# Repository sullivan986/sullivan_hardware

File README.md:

# sullivan_hardware
Some open-source hardware designed by Kicad.

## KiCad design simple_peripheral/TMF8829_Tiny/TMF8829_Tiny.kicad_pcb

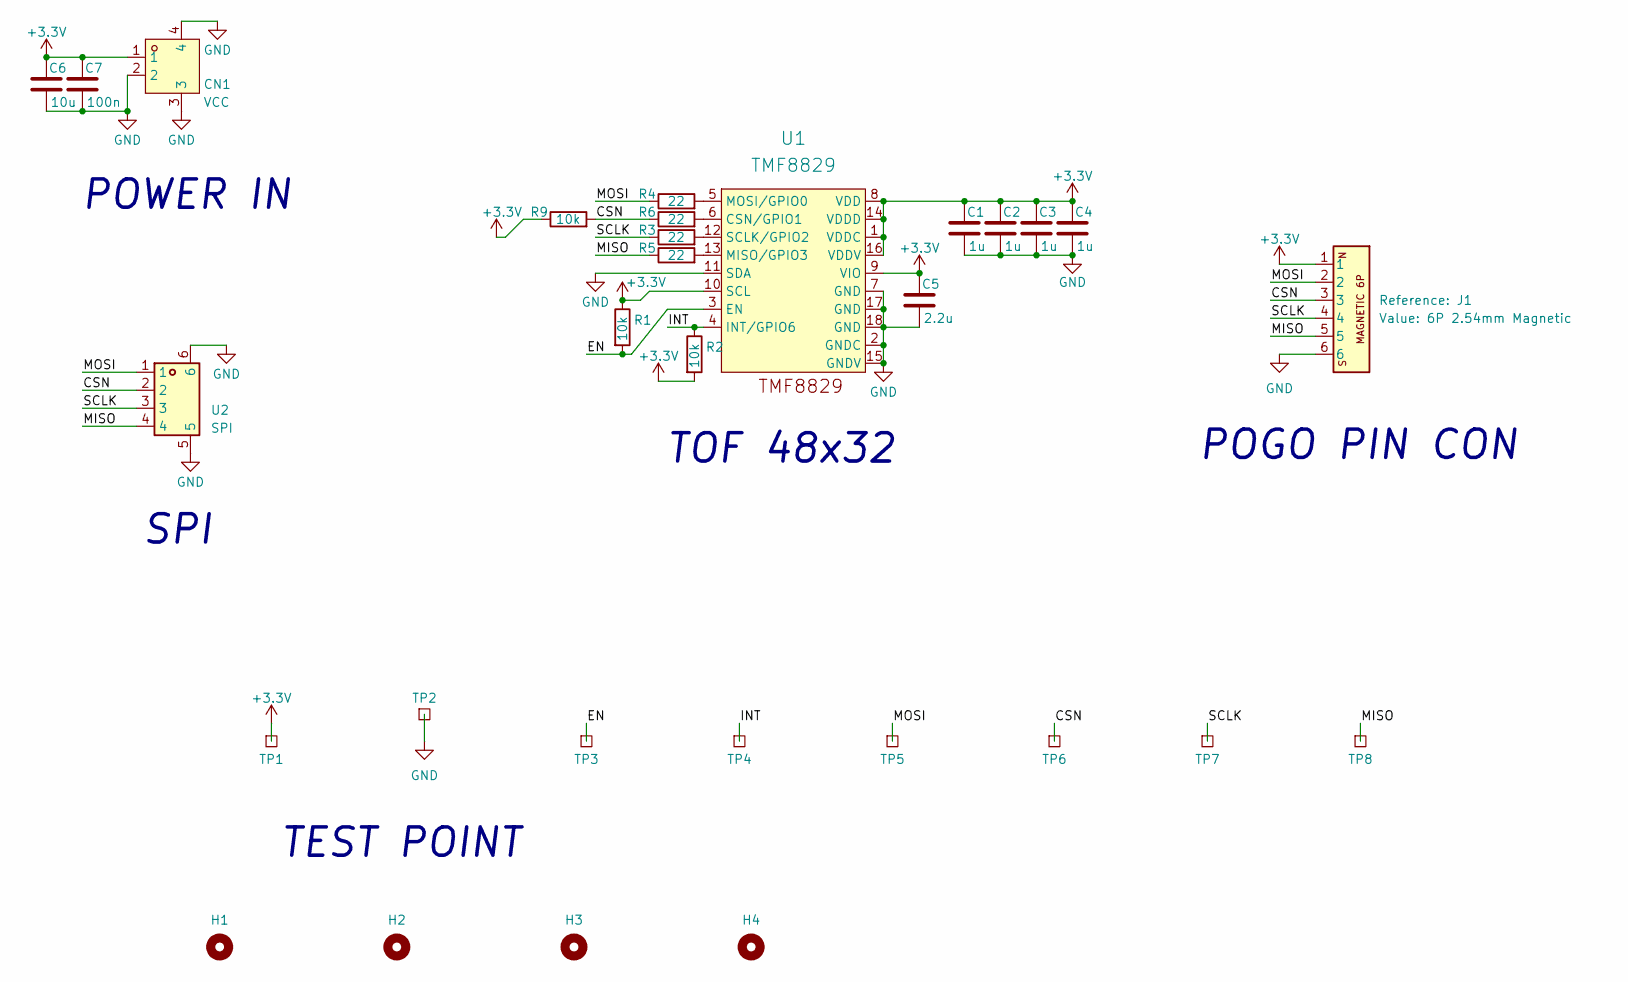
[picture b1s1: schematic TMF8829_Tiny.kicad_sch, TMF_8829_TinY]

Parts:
C1, C2, C3, C4: 1u; C_0402_1005Metric
C5: 2.2u; C_0402_1005Metric
C6: 10u; C_0402_1005Metric
C7: 100n; C_0402_1005Metric
CN1: VCC; CONN-TH_2P-P1.25_XUNPU_WAFER-GH1.25-2PWB; MPN WAFER-GH1.25-2PWB; LCSC Part C3029377
H1, H2, H3, H4: MountingHole; MountingHole_2.2mm_M2
J1: 6P 2.54mm Magnetic; Connector_Magnetic_1x06_P2.54mm_RA
R1, R2, R9: 10k; R_0402_1005Metric
R3, R4, R5, R6: 22; R_0402_1005Metric
TP1: 3V3; TestPoint_Pad_2.0x2.0mm
TP2: GND; TestPoint_Pad_2.0x2.0mm
TP3: EN; TestPoint_Pad_2.0x2.0mm
TP4: INT; TestPoint_Pad_2.0x2.0mm
TP5: MOSI; TestPoint_Pad_2.0x2.0mm
TP6: CSN; TestPoint_Pad_2.0x2.0mm
TP7: SCLK; TestPoint_Pad_2.0x2.0mm
TP8: MISO; TestPoint_Pad_2.0x2.0mm
U1: TMF8829; Manufacturer Part Numbe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 TMF8829
U2: SPI; CONN-SMD_4P-P1.25_XUNPU_WAFER-GH1.25-4PWB; LCSC Part C3029379

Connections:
+3.3V: C1.1, C2.1, C3.1, C4.1, C5.1, C6.1, C7.1, CN1.1, J1.1, R1.1, R2.2, R9.1, TP1.1 (1_1), U1.1 (VDDC), U1.8 (VDD), U1.9 (VIO), U1.10 (SCL), U1.14 (VDDD), U1.16 (VDDV)
/CSN: J1.3, R6.1, R9.2, TP6.1 (1_1), U2.2
/EN: R1.2, TP3.1 (1_1), U1.3 (EN)
/INT: R2.1, TP4.1 (1_1), U1.4 (INT/GPIO6)
/MISO: J1.5, R5.1, TP8.1 (1_1), U2.4
/MOSI: J1.2, R4.1, TP5.1 (1_1), U2.1
/SCLK: J1.4, R3.1, TP7.1 (1_1), U2.3
GND: C1.2, C2.2, C3.2, C4.2, C5.2, C6.2, C7.2, CN1.2, CN1.3, CN1.4, J1.6, TP2.1 (1_1), U1.2 (GNDC), U1.7 (GND), U1.11 (SDA), U1.15 (GNDV), U1.17 (GND), U1.18 (GND), U2.5, U2.6
unnamed: R6.2, U1.6 (CSN/GPIO1)
unnamed: R5.2, U1.13 (MISO/GPIO3)
unnamed: R4.2, U1.5 (MOSI/GPIO0)
unnamed: R3.2, U1.12 (SCLK/GPIO2)

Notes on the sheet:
POGO PIN CON
TOF 48x32
POWER IN
SPI
TEST POINT

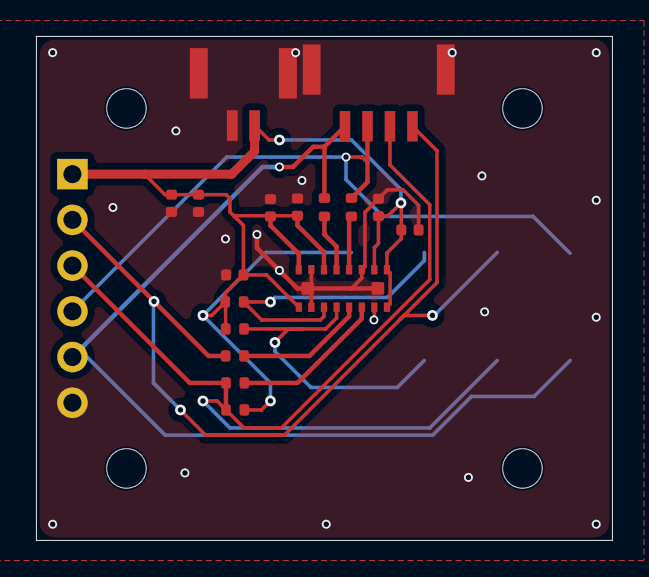
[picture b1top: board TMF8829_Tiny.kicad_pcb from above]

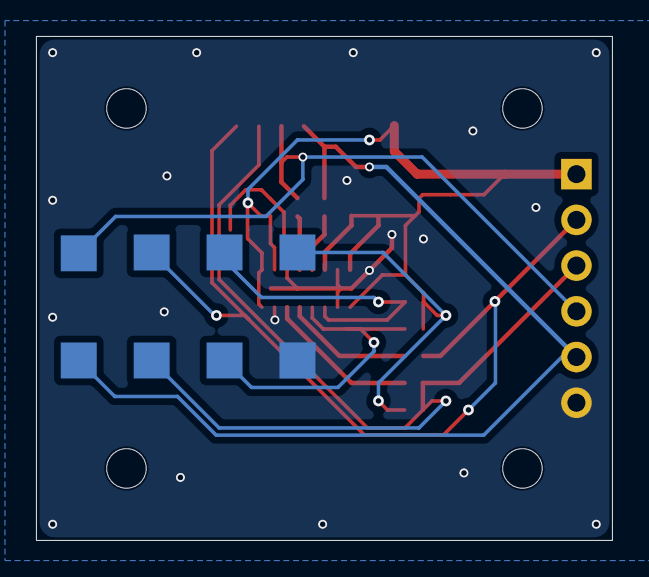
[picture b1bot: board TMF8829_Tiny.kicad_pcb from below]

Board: 2 copper layers, 32.0 x 28.0 mm, 30 parts (8 on the bottom side), 12 nets.

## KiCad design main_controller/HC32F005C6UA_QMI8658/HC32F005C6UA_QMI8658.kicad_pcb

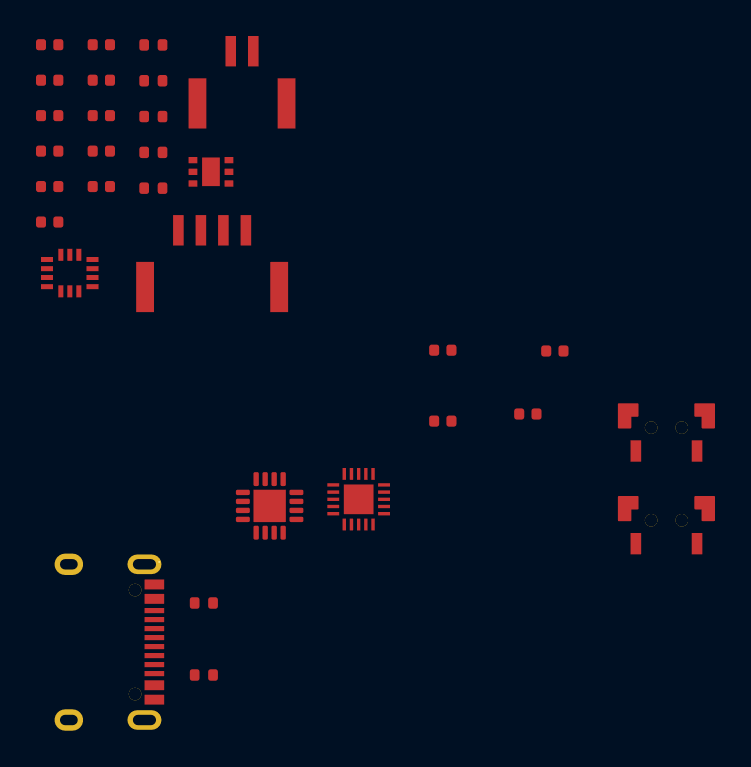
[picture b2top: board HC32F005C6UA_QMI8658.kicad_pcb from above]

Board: 2 copper layers, 31 parts (0 on the bottom side), 20 nets, no tracks yet.

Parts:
C3, C5, C9, C11, C12, C13, C15, C16, C17: 100n; C_0402_1005Metric
C4: 10u; C_0402_1005Metric
C6, C7, C8: 1u; C_0402_1005Metric
C10, C14: 4.7u; C_0402_1005Metric
CN1: WAFER-GH1.25-2PWB; CONN-TH_2P-P1.25_XUNPU_WAFER-GH1.25-2PWB
R1, R2, R4: 5.1k; R_0402_1005Metric
R3, R6, R7: 10k; R_0402_1005Metric
R5: 1k; R_0402_1005Metric
SW1, SW2: BTN; SW-SMD_2P-TS24CA
U1: HC32F005C6UA; QFN-20_L3.0-W3.0-P0.40-BL-EP1.7
U2: QMI8658B_C5380158; LGA-14_L3.0-W2.5-P0.50-TL
U3: TLV75733PDRVR; TDFN-6_L2.0-W2.0-P0.65-TL-EP
U4: CH343P; WCH_QFN-16-1EP_3x3mm_P0.5mm_EP1.8x1.8mm
U5: WAFER-GH1.25-4PWB; CONN-SMD_4P-P1.25_XUNPU_WAFER-GH1.25-4PWB
USB2: TYPE-C 16PIN 2MD(073); USB-C-SMD_TYPE-C-16PIN-2MD-073

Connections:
+3V3: C6.2, C8.1, C9.1, C11.1, C14.1, C15.1, R3.1, R4.1, R5.2, R6.1, R7.1, U1.6 (VDD), U2.5 (VDDIO), U2.8 (VDD), U2.12 (CS), U3.1 (OUT), U4.1 (VIO), U5.1
+5V: C4.2, C5.2, C7.1, U3.4 (EN), U3.6 (IN), U4.3 (VDD5), U4.9 (VBUS), USB2.A4B9 (VBUS), USB2.B4A9 (VBUS)
/BTN: C17.1, R7.2, SW2.2, U1.18 (P34/AIN4/VCIN4)
/BTN_EXT: C16.1, CN1.1, R6.2, U1.17 (P33/AIN3/VCIN3)
/CH343_RTS: C12.1, R3.2, SW1.1, U1.1 (RESETB/P00), U4.13 (~RTS)
/CH343_RX: U1.19 (P35/AIN5/VCIN5), U4.5 (RXD)
/CH343_TX: U1.20 (P36/AIN6/VCIN6/AVREF), U4.4 (TXD)
/I2C_SCL: R4.2, U1.9 (P14), U2.13 (SCL)
/I2C_SDA: R5.1, U1.8 (P15), U2.14 (SDA)
/INT1: U1.7 (LVDIN1/P03), U2.4 (INT1)
/INT2: U1.10 (LVDIN2/VCIN0/P23), U2.9 (INT2)
/URX1: U1.3 (XTHO/AIN8/P02), U5.3
/UTX1: U1.2 (XTHI/AIN7/VCIN7/P01), U5.2
GND: C3.1, C4.1, C5.1, C6.1, C7.2, C8.2, C9.2, C10.1, C11.2, C12.2, C13.1, C14.2, C15.2, C16.2, C17.2, CN1.2, CN1.3, CN1.4, R1.1, R2.1, SW1.2, SW2.1, U1.4 (VSS), U1.21 (EP), U2.1 (SDO/SA0), U2.6 (GND), U2.7 (GND), U3.3 (GND), U3.7 (EP), U4.2 (GND), U4.17 (GND_EPAD), U5.4, U5.5, U5.6, USB2.13 (EH), USB2.14 (EH), USB2.A1B12 (GND), USB2.B1A12 (GND)
unnamed: C10.2, C13.2, U1.5 (VCAP)
unnamed: U4.7 (UD+), USB2.B6 (Dp2), USB2.B7 (Dn2)
unnamed: U4.8 (UD-), USB2.A6 (Dp1), USB2.A7 (Dn1)
unnamed: C3.2, U4.6 (V3_{OUT})
unnamed: R2.2, USB2.A5 (CC1)
unnamed: R1.2, USB2.B5 (CC2)
